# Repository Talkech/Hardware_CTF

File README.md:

# Hardware CTF Board

A custom PCB used as a hardware capture the flag challenge for those who wants to learn get into hardware hacking.

The goal is to recover a flag from each stage using real hardware-hacking techniques, then submit it over a serial console. Each solved stage lights an LED, updates a score counter, and displays a message and the score on an OLED display.

*Board:* STM32F103C8T6, 2-layer

## Stages

1. Hidden UART console (Finding unlabelled pads, identifying the baud rate)
2. SPI flash dump
3. I2C bus sniffing (Capturing and decoding a bus with a logic analyser)
4. Firmware reverse engineering (Static analysis of an ARM binary)
5. SWD debug access (Halting the core and reading memory)
6. RF capture & replay (SDR capture and retransmission at 433MHz)
7. Timing side-channel (Exploiting a non-constant-time comparison)

## Status
- [x] Schematic
- [x] PCB layout
- [ ] Firmware
- [ ] Fabrication & assembly

## Author

Talkech

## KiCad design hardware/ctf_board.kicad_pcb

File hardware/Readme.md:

# Hardware
 
Hardware Hacking Training Board V1
 
## Schematic

## PCB layout
 
| Top | Bottom |
|-----|--------|
|  |  |
 
## 3D view
 
| Front | Back |
|-------|------|
|  |  |

## Software

Kicad 10

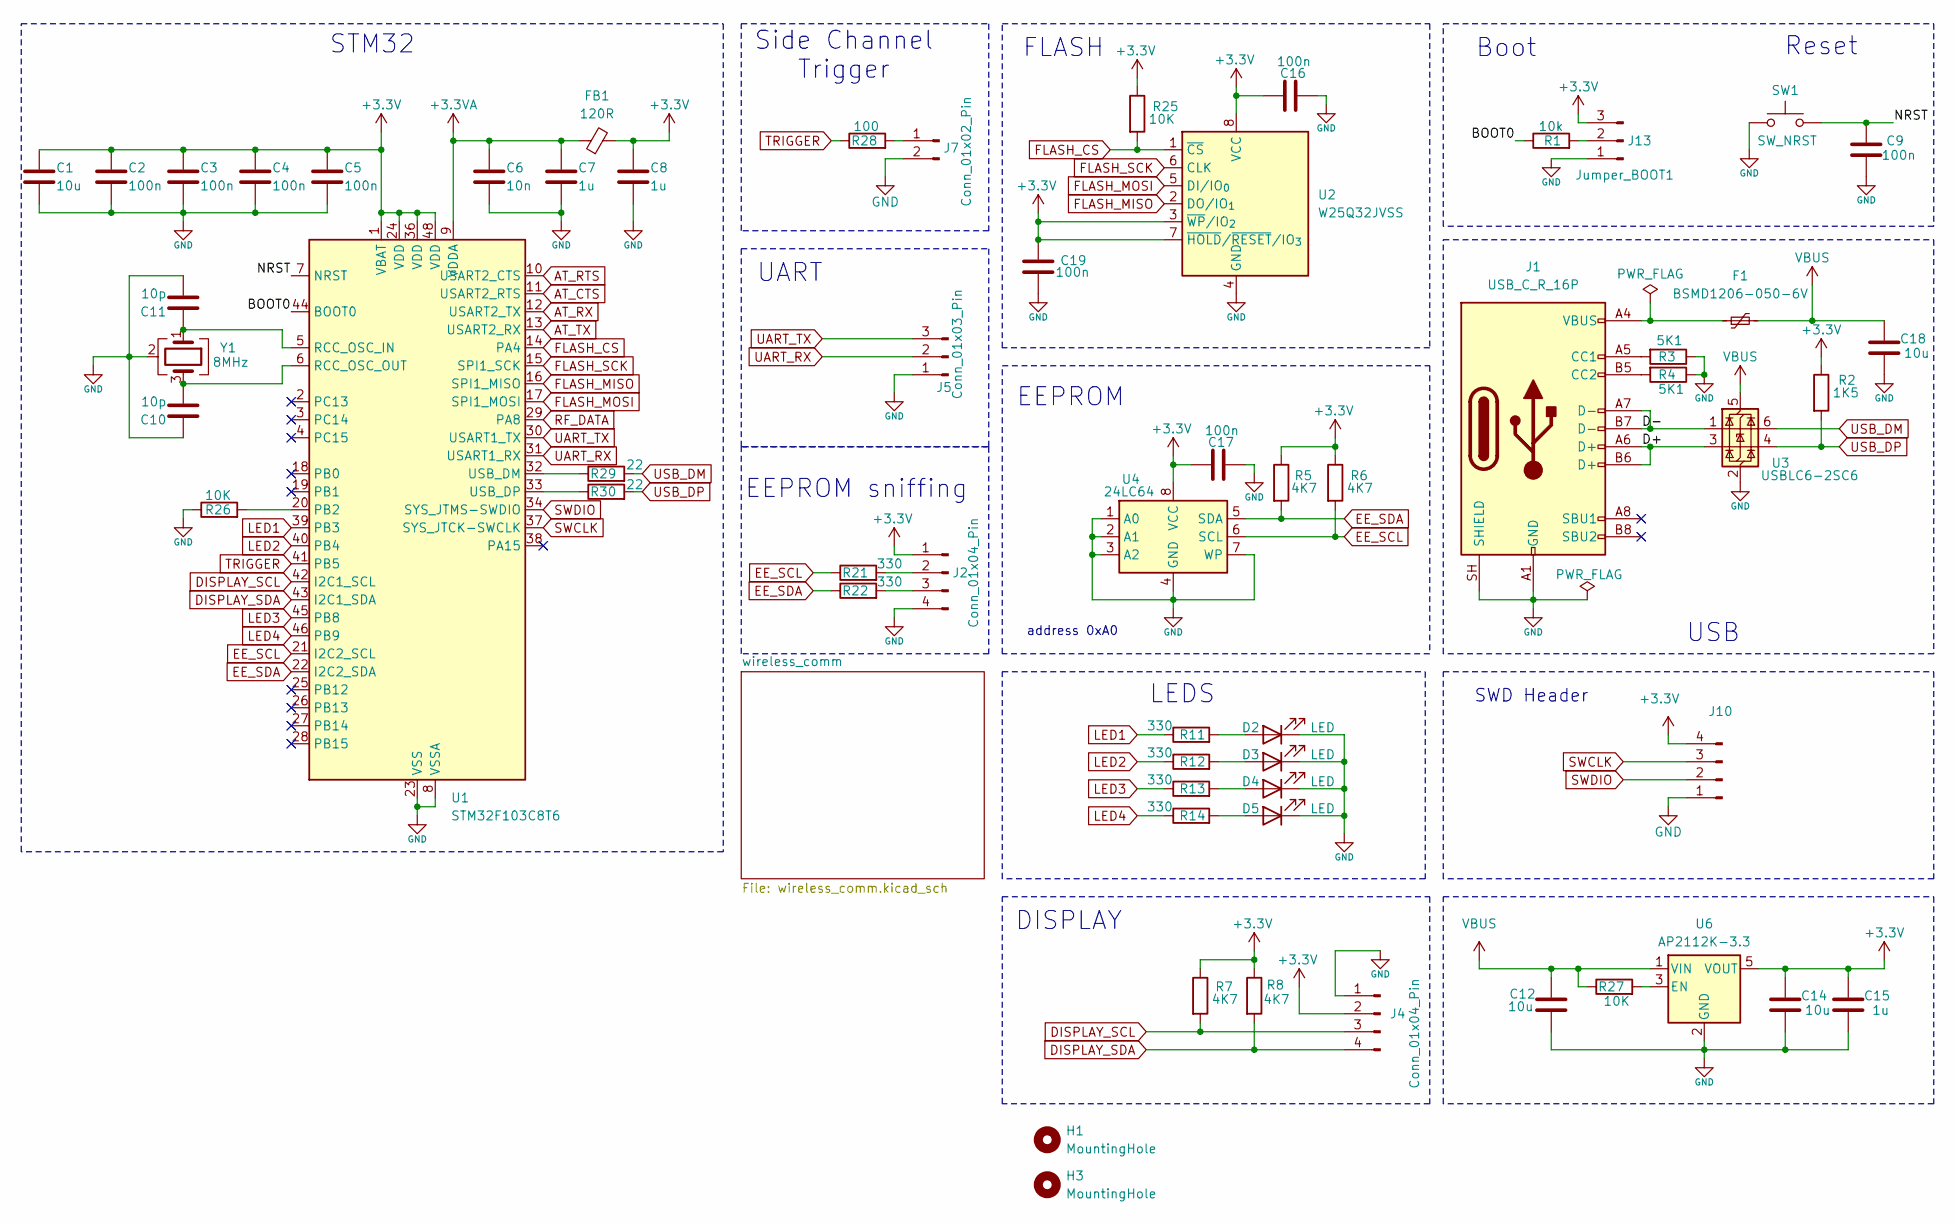
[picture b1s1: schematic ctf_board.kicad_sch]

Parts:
C1, C12, C14, C18: 10u; C_0603_1608Metric_Pad1.08x0.95mm_HandSolder
C2, C3, C4, C5, C9, C16, C17, C19: 100n; C_0603_1608Metric_Pad1.08x0.95mm_HandSolder
C6: 10n; C_0603_1608Metric_Pad1.08x0.95mm_HandSolder
C7, C8, C15: 1u; C_0603_1608Metric_Pad1.08x0.95mm_HandSolder
C10, C11: 10p; C_0603_1608Metric_Pad1.08x0.95mm_HandSolder
D2, D3, D4, D5: LED; LED_0603_1608Metric_Pad1.05x0.95mm_HandSolder
F1: BSMD1206-050-6V; Fuse_1206_3216Metric_Pad1.42x1.75mm_HandSolder
FB1: 120R; Fuse_0603_1608Metric_Pad1.05x0.95mm_HandSolder
H1, H3: MountingHole; MountingHole_3.2mm_M3_Pad
J1: USB_C_R_16P; USB_C_Receptacle_GCT_USB4105-xx-A_16P_TopMnt_Horizontal
J2, J4, J10: Conn_01x04_Pin; PinHeader_1x04_P2.54mm_Vertical
J5: Conn_01x03_Pin; PinHeader_1x03_P2.54mm_Vertical
J7: Conn_01x02_Pin; PinHeader_1x02_P2.54mm_Vertical
J13: Jumper_BOOT1; PinHeader_1x03_P2.54mm_Vertical
R1: 10k; R_0603_1608Metric_Pad0.98x0.95mm_HandSolder
R2: 1K5; R_0603_1608Metric_Pad0.98x0.95mm_HandSolder
R3, R4: 5K1; R_0603_1608Metric_Pad0.98x0.95mm_HandSolder
R5, R6, R7, R8: 4K7; R_0603_1608Metric_Pad0.98x0.95mm_HandSolder
R11, R12, R13, R14, R21, R22: 330; R_0603_1608Metric_Pad0.98x0.95mm_HandSolder
R25, R26, R27: 10K; R_0603_1608Metric_Pad0.98x0.95mm_HandSolder
R28: 100; R_0603_1608Metric_Pad0.98x0.95mm_HandSolder
R29, R30: 22; R_0603_1608Metric_Pad0.98x0.95mm_HandSolder
SW1: SW_NRST; SW_Tactile_SPST_NO_Straight_CK_PTS636Sx25SMTRLFS
U1: STM32F103C8T6; LQFP-48_7x7mm_P0.5mm
U2: W25Q32JVSS; SOIC-8_5.3x5.3mm_P1.27mm
U3: USBLC6-2SC6; SOT-23-6
U4: 24LC64; SOIC-8_3.9x4.9mm_P1.27mm
U6: AP2112K-3.3; SOT-23-5
Y1: 8MHz; Crystal_SMD_3225-4Pin_3.2x2.5mm_HandSoldering

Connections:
+3.3V: C1.1, C2.1, C3.1, C4.1, C5.1, C8.1, C14.2, C15.2, C16.2, C17.2, C19.1, FB1.2, J2.1, J4.2, J10.4, J13.3, R2.1, R5.1, R6.1, R7.1, R8.1, R25.1, U1.1 (VBAT), U1.24 (VDD), U1.36 (VDD), U1.48 (VDD), U2.3 (~WP/IO_{2}), U2.7 (~HOLD/~RESET/IO_{3}), U2.8 (VCC), U4.8 (VCC), U6.5 (VOUT); also elsewhere on the board
+3.3VA: C6.1, C7.1, FB1.1, U1.9 (VDDA)
/BOOT0: R1.1, U1.44 (BOOT0)
/D+: J1.A6 (D+), J1.B6 (D+), U3.3 (I/O2)
/D-: J1.A7 (D-), J1.B7 (D-), U3.1 (I/O1)
/NRST: C9.2, SW1.2, U1.7 (NRST)
AT_CTS: U1.11 (USART2_RTS); also elsewhere on the board
AT_RTS: U1.10 (USART2_CTS); also elsewhere on the board
AT_RX: U1.12 (USART2_TX); also elsewhere on the board
AT_TX: U1.13 (USART2_RX); also elsewhere on the board
DISPLAY_SCL: J4.3, R7.2, U1.42 (I2C1_SCL)
DISPLAY_SDA: J4.4, R8.2, U1.43 (I2C1_SDA)
EE_SCL: R6.2, R21.1, U1.21 (I2C2_SCL), U4.6 (SCL)
EE_SDA: R5.2, R22.1, U1.22 (I2C2_SDA), U4.5 (SDA)
FLASH_CS: R25.2, U1.14 (PA4), U2.1 (~CS)
FLASH_MISO: U1.16 (SPI1_MISO), U2.2 (DO/IO_{1})
FLASH_MOSI: U1.17 (SPI1_MOSI), U2.5 (DI/IO_{0})
FLASH_SCK: U1.15 (SPI1_SCK), U2.6 (CLK)
GND: C1.2, C2.2, C3.2, C4.2, C5.2, C6.2, C7.2, C8.2, C9.1, C10.1, C11.2, C12.1, C14.1, C15.1, C16.1, C17.1, C18.1, C19.2, D2.1 (K), D3.1 (K), D4.1 (K), D5.1 (K), J1.A1 (GND), J1.A12 (GND), J1.B1 (GND), J1.B12 (GND), J1.SH (SHIELD), J2.4, J4.1, J5.1, J7.2, J10.1, J13.1, R3.1, R4.1, R26.1, SW1.1, U1.8 (VSSA), U1.23 (VSS), U1.35 (VSS), U1.47 (VSS), U2.4 (GND), U3.2 (GND), U4.1 (A0), U4.2 (A1), U4.3 (A2), U4.4 (GND), U4.7 (WP), U6.2 (GND), Y1.2 (G), Y1.4 (G); also elsewhere on the board
LED1: R11.1, U1.39 (PB3)
LED2: R12.1, U1.40 (PB4)
LED3: R13.1, U1.45 (PB8)
LED4: R14.1, U1.46 (PB9)
unnamed: D2.2 (A), R11.2
unnamed: D3.2 (A), R12.2
unnamed: D4.2 (A), R13.2
unnamed: D5.2 (A), R14.2
unnamed: F1.1, J1.A4 (VBUS), J1.A9 (VBUS), J1.B4 (VBUS), J1.B9 (VBUS)
unnamed: J1.A5 (CC1), R3.2
unnamed: J1.B5 (CC2), R4.2
unnamed: J2.2, R21.2
unnamed: J2.3, R22.2
unnamed: J7.1, R28.2
unnamed: J13.2, R1.2
unnamed: R29.1, U1.32 (USB_DM)
unnamed: R30.1, U1.33 (USB_DP)
unnamed: R26.2, U1.20 (PB2)
unnamed: C11.1, U1.5 (RCC_OSC_IN), Y1.1
unnamed: C10.2, U1.6 (RCC_OSC_OUT), Y1.3
unnamed: R27.2, U6.3 (EN)
RF_DATA: U1.29 (PA8); also elsewhere on the board
SWCLK: J10.3, U1.37 (SYS_JTCK-SWCLK)
SWDIO: J10.2, U1.34 (SYS_JTMS-SWDIO)
TRIGGER: R28.1, U1.41 (PB5)
UART_RX: J5.2, U1.31 (USART1_RX)
UART_TX: J5.3, U1.30 (USART1_TX)
USB_DM: R29.2, U3.6 (I/O1)
USB_DP: R2.2, R30.2, U3.4 (I/O2)
VBUS: C12.2, C18.2, F1.2, R27.1, U3.5 (VBUS), U6.1 (VIN)

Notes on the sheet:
EEPROM sniffing
Boot
UART
LEDS
SWD Header
Side Channel Trigger
address 0xA0
USB
STM32
Reset
DISPLAY
FLASH
EEPROM

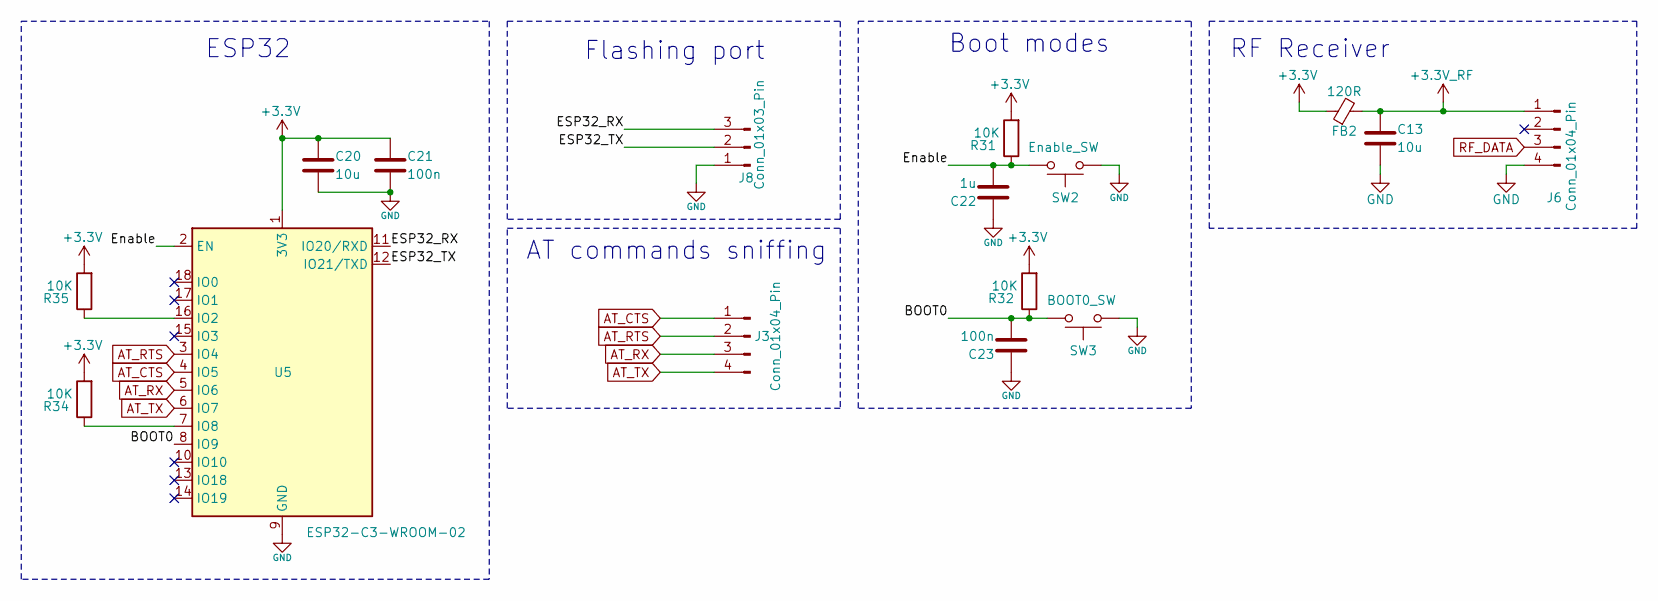
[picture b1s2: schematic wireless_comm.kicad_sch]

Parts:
C13, C20: 10u; C_0603_1608Metric_Pad1.08x0.95mm_HandSolder
C21, C23: 100n; C_0603_1608Metric_Pad1.08x0.95mm_HandSolder
C22: 1u; C_0603_1608Metric_Pad1.08x0.95mm_HandSolder
FB2: 120R; Fuse_0603_1608Metric_Pad1.05x0.95mm_HandSolder
J3, J6: Conn_01x04_Pin; PinHeader_1x04_P2.54mm_Vertical
J8: Conn_01x03_Pin; PinHeader_1x03_P2.54mm_Vertical
R31, R32, R34, R35: 10K; R_0603_1608Metric_Pad0.98x0.95mm_HandSolder
SW2: Enable_SW; SW_Tactile_SPST_NO_Straight_CK_PTS636Sx25SMTRLFS
SW3: BOOT0_SW; SW_Tactile_SPST_NO_Straight_CK_PTS636Sx25SMTRLFS
U5: ESP32-C3-WROOM-02

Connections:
+3.3V: C20.1, C21.1, FB2.1, R31.2, R32.2, R34.2, R35.2, U5.1 (3V3); also elsewhere on the board
+3.3V_RF: C13.1, FB2.2, J6.1
/wireless_comm/BOOT0: C23.2, R32.1, SW3.2, U5.8 (IO9)
/wireless_comm/ESP32_RX: J8.3, U5.11 (IO20/RXD)
/wireless_comm/ESP32_TX: J8.2, U5.12 (IO21/TXD)
/wireless_comm/Enable: C22.2, R31.1, SW2.2, U5.2 (EN)
AT_CTS: J3.1, U5.4 (IO5); also elsewhere on the board
AT_RTS: J3.2, U5.3 (IO4); also elsewhere on the board
AT_RX: J3.3, U5.5 (IO6); also elsewhere on the board
AT_TX: J3.4, U5.6 (IO7); also elsewhere on the board
GND: C13.2, C20.2, C21.2, C22.1, C23.1, J6.4, J8.1, SW2.1, SW3.1, U5.9 (GND), U5.19 (GND); also elsewhere on the board
unnamed: R35.1, U5.16 (IO2)
unnamed: R34.1, U5.7 (IO8)
RF_DATA: J6.3; also elsewhere on the board

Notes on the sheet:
Boot modes
Flashing port
ESP32
RF Receiver
AT commands sniffing

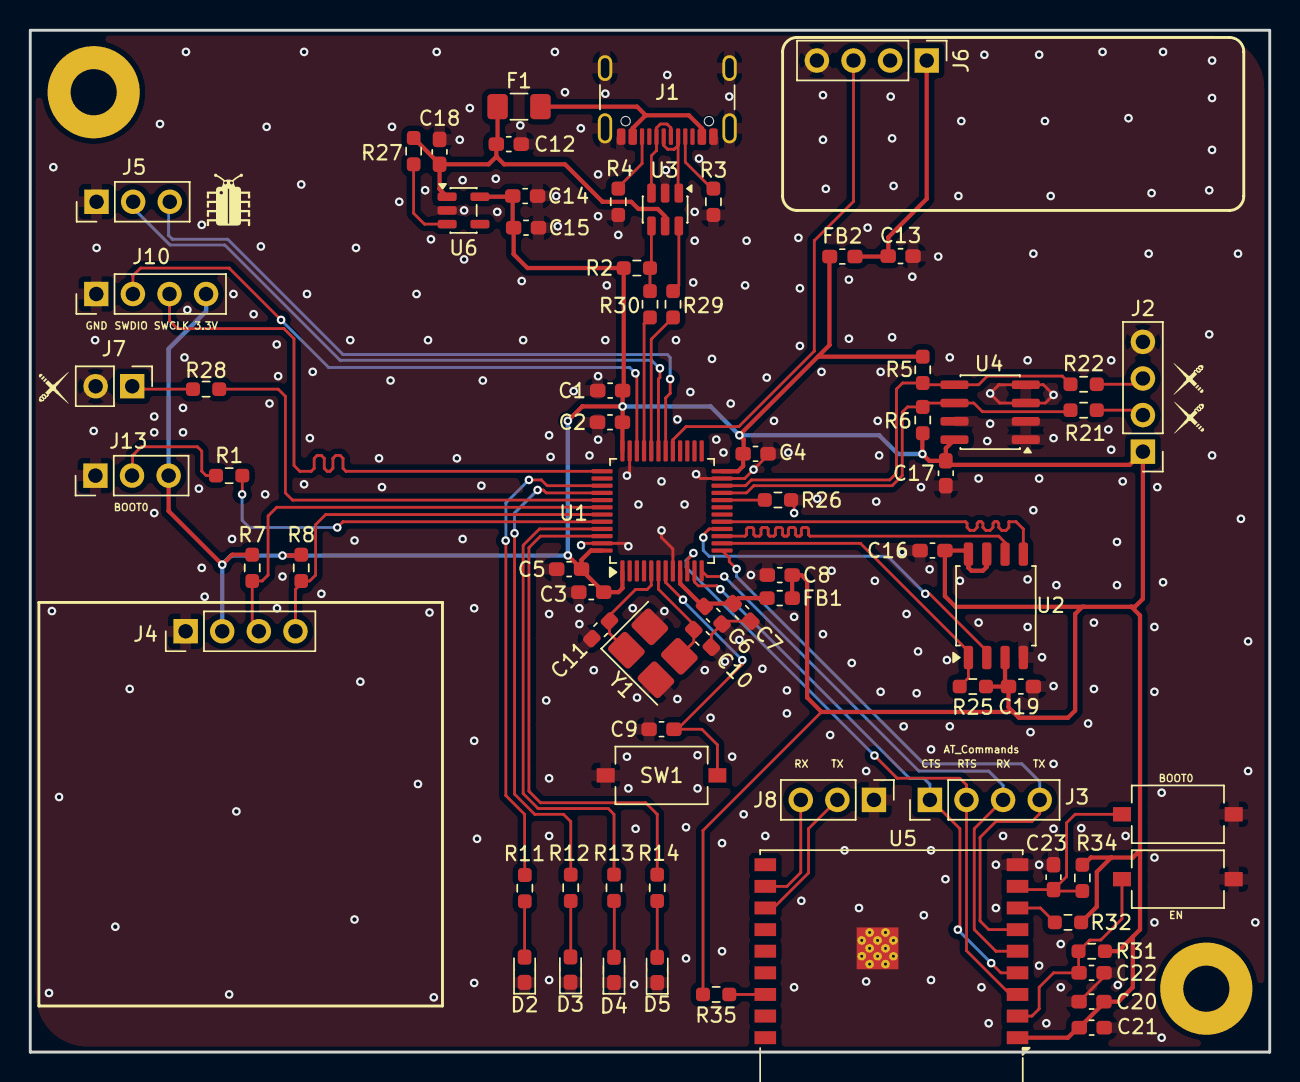
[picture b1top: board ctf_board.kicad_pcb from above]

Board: 2 copper layers, 86.0 x 70.9 mm, 76 parts (0 on the bottom side), 56 nets.
